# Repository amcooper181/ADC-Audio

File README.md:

# ESP32 Analog to Digital Streamer

## Overview

The **ESP32 Analog to Digital Streamer** is a project designed to capture analog audio signals and stream them using the ESP32 microcontroller. The PCM1862 ADC this project is based on is feature-rich, highly customizable, and offers a 100dB+ signal to noise ratio.

## Features

- **High-Quality Audio Capture:** Utilizes the PCM1862 ADC for precise analog-to-digital conversion.
- **Real-Time Streaming:** Stream audio data over Wi-Fi using the ESP32's built-in capabilities.
- **High Sample Rate:** 96 kHz at 24 bits
- **Low Latency:** Optimized for low-latency streaming to ensure real-time audio processing.
- **Input Options:** This device allows for inputs via a 3.5mm TRRS connector or RCA cables
- **Input Levels:** Supports line-level inputs. The PCM1862 has a configurable, 2 level gain amplifier that can be used for phono inputs, but for the best quality a dedicated, external amplifier is recommended.

## Getting Started

### Hardware

- **Prototype Stage** The KiCad files are available for the first prototype, located in [adcesp32_kicad/](./adcesp32_kicad//)
- **Power Supply** The device requires a USB-C power supply.

### Software

- **Building the Project** All files needed to build the project in PlatformIO are included in this repo
- **Basic Functionality** As of now, the software included in this repo will allow the user to convert an analog input to digital output. An I2S amplifier can be can be connected to listen to playback.
- **Buffered Data** The data is buffered before being sent to the DOUT pin on the PCM1862. This was done to prototype data processing speed.
- **Work In Progress** The software will be updated, improved, and finalized upon finalization of the hardware. The hardware is currently on order, and 5 demo boards should arrive by 9/1/2024

### License
This project is licensed under the GPL V3 License. See the [LICENSE](./LICENSE) file for details.

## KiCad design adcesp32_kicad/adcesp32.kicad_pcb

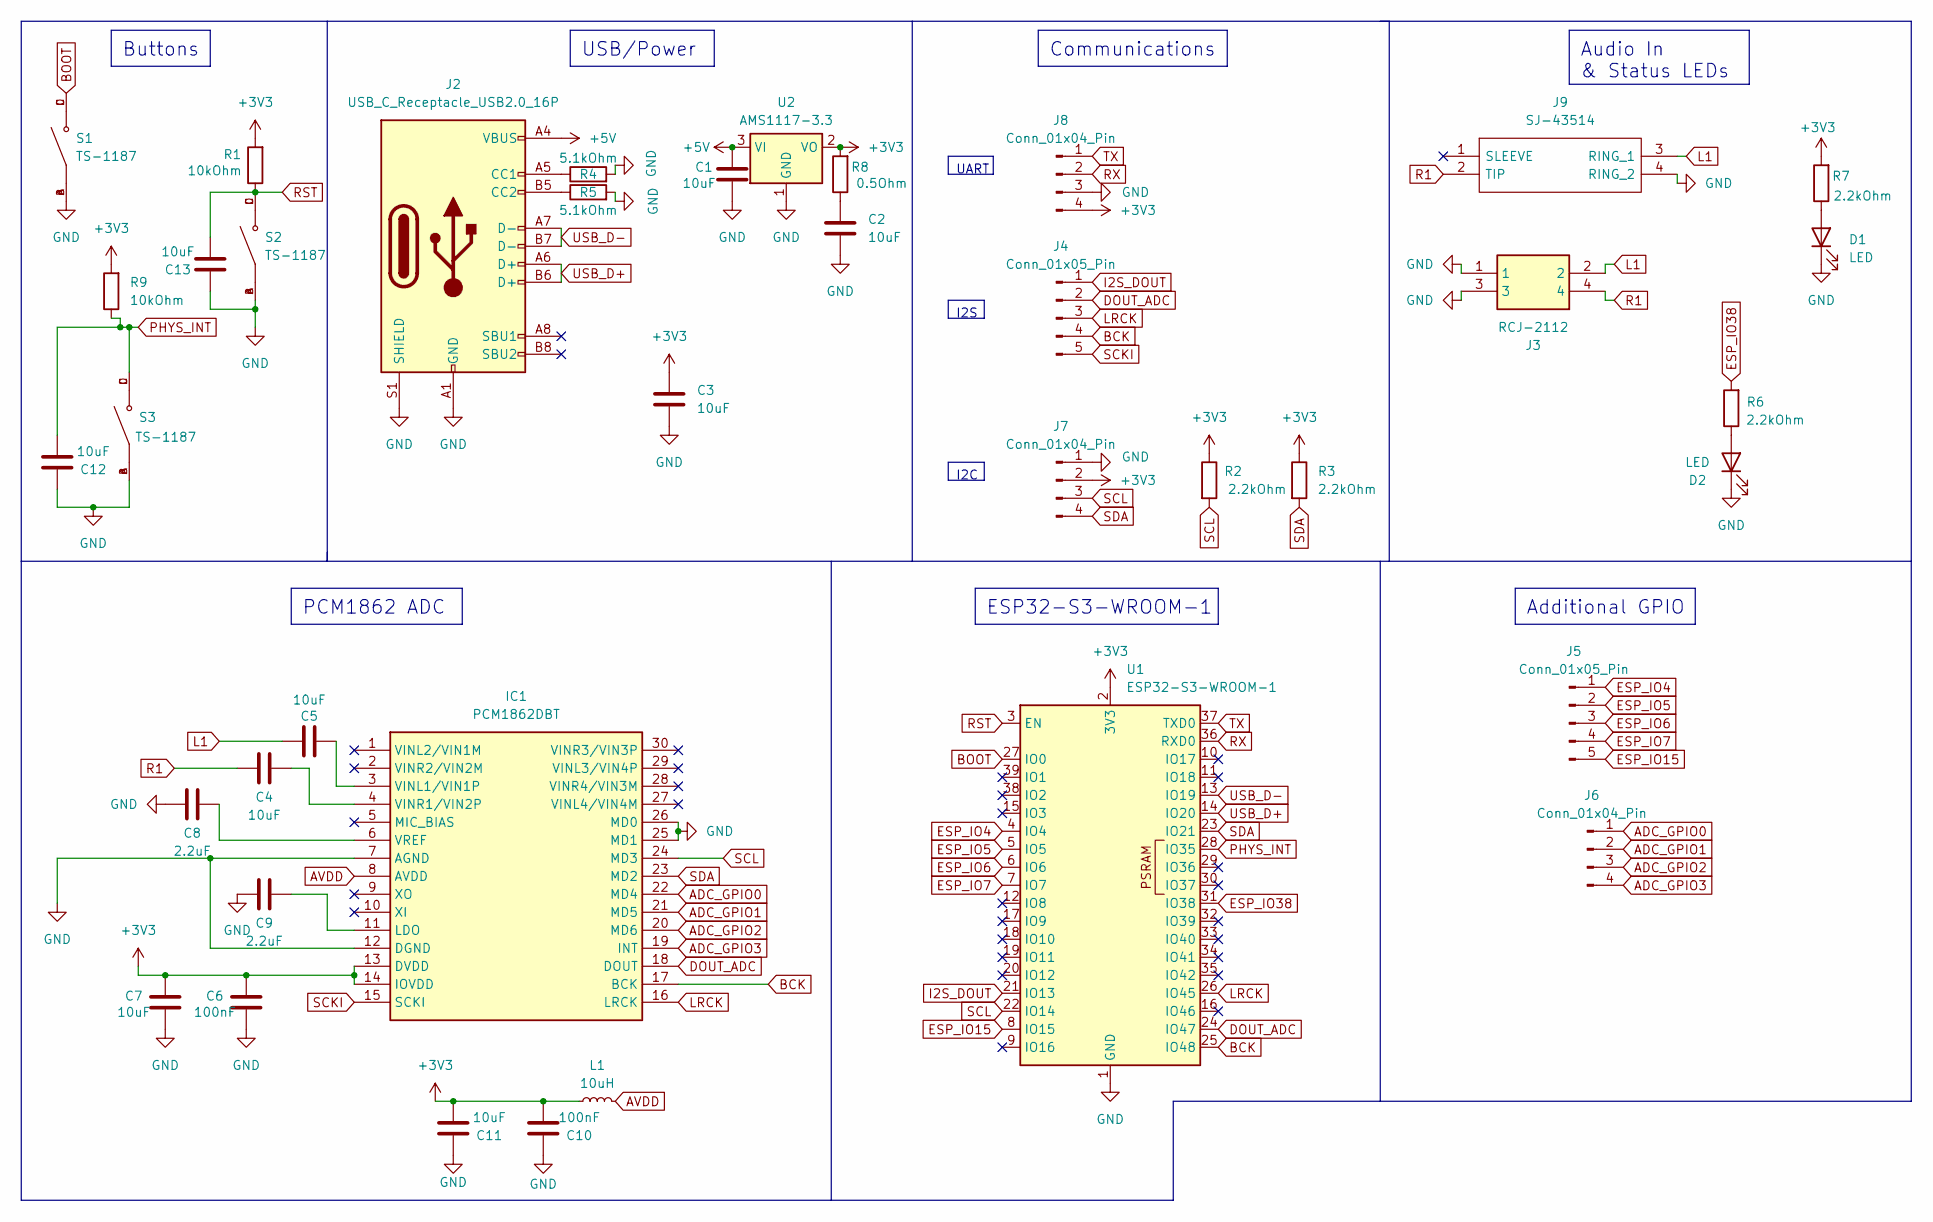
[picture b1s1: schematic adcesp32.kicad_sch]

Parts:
C1, C2, C3, C4, C5, C7, C11, C12, C13: 10uF; C_0402_1005Metric
C6, C10: 100nF; C_0402_1005Metric
C8, C9: 2.2uF; C_0402_1005Metric
D1, D2: LED; R_0805_2012Metric
IC1: PCM1862DBT; SOP50P640X120-30N; Mouser Part Number 595-PCM1862DBT
J2: USB_C_Receptacle_USB2.0_16P; USB_C_Receptacle_HRO_TYPE-C-31-M-12
J3: RCJ-2112; RCJ2112; Mouser Part Number 490-RCJ-2112
J4, J5: Conn_01x05_Pin; PinHeader_1x05_P2.54mm_Vertical
J6, J7, J8: Conn_01x04_Pin; PinHeader_1x04_P2.54mm_Vertical
J9: SJ-43514; SJ43514; Mouser Part Number 490-SJ-43514
L1: 10uH; L_0805_2012Metric
R1, R9: 10kOhm; R_0402_1005Metric
R2, R3, R6, R7: 2.2kOhm; R_0603_1608Metric
R4, R5: 5.1kOhm; R_0402_1005Metric
R8: 0.5Ohm; R_0603_1608Metric
S1, S2, S3: TS-1187; SW_TS-1187A-B-A-B; PARTREV A0
U1: ESP32-S3-WROOM-1
U2: AMS1117-3.3; SOT-223-3_TabPin2

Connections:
+3V3: C3.1, C6.2, C7.2, C10.2, C11.2, IC1.13 (DVDD), IC1.14 (IOVDD), J7.2, J8.4, L1.1, R1.2, R2.1, R3.1, R7.2, R8.2, R9.2, U1.2 (3V3), U2.2 (VO)
+5V: C1.1, J2.A4 (VBUS), J2.A9 (VBUS), J2.B4 (VBUS), J2.B9 (VBUS), U2.3 (VI)
ADC_GPIO0: IC1.22 (MD4), J6.1
ADC_GPIO1: IC1.21 (MD5), J6.2
ADC_GPIO2: IC1.20 (MD6), J6.3
ADC_GPIO3: IC1.19 (INT), J6.4
AVDD: IC1.8 (AVDD), L1.2
BCK: IC1.17 (BCK), J4.4, U1.25 (IO48)
BOOT: S1.C, S1.D, U1.27 (IO0)
DOUT_ADC: IC1.18 (DOUT), J4.2, U1.24 (IO47)
ESP_IO4: J5.1, U1.4 (IO4)
ESP_IO5: J5.2, U1.5 (IO5)
ESP_IO6: J5.3, U1.6 (IO6)
ESP_IO7: J5.4, U1.7 (IO7)
ESP_IO15: J5.5, U1.8 (IO15)
ESP_IO38: R6.2, U1.31 (IO38)
GND: C1.2, C2.2, C3.2, C6.1, C7.1, C8.1, C9.1, C10.1, C11.1, C12.1, C13.1, D1.1 (K), D2.1 (K), IC1.7 (AGND), IC1.12 (DGND), IC1.25 (MD1), IC1.26 (MD0), J2.A1 (GND), J2.A12 (GND), J2.B1 (GND), J2.B12 (GND), J2.S1 (SHIELD), J3.1, J3.3, J7.1, J8.3, J9.4 (RING_2), R4.2, R5.2, S1.A, S1.B, S2.A, S2.B, S3.A, S3.B, U1.1 (GND), U1.40 (GND), U1.41 (GND), U2.1 (GND)
I2S_DOUT: J4.1, U1.21 (IO13)
L1: C5.1, J3.2, J9.3 (RING_1)
LRCK: IC1.16 (LRCK), J4.3, U1.26 (IO45)
unnamed: C2.1, R8.1
unnamed: D1.2 (A), R7.1
unnamed: D2.2 (A), R6.1
unnamed: C9.2, IC1.11 (LDO)
unnamed: C5.2, IC1.3 (VINL1/VIN1P)
unnamed: C4.2, IC1.4 (VINR1/VIN2P)
unnamed: C8.2, IC1.6 (VREF)
unnamed: J2.A5 (CC1), R4.1
unnamed: J2.B5 (CC2), R5.1
PHYS_INT: C12.2, R9.1, S3.C, S3.D, U1.28 (IO35)
R1: C4.1, J3.4, J9.2 (TIP)
RST: C13.2, R1.1, S2.C, S2.D, U1.3 (EN)
RX: J8.2, U1.36 (RXD0)
SCKI: IC1.15 (SCKI), J4.5
SCL: IC1.24 (MD3), J7.3, R2.2, U1.22 (IO14)
SDA: IC1.23 (MD2), J7.4, R3.2, U1.23 (IO21)
TX: J8.1, U1.37 (TXD0)
USB_D+: J2.A6 (D+), J2.B6 (D+), U1.14 (IO20)
USB_D-: J2.A7 (D-), J2.B7 (D-), U1.13 (IO19)

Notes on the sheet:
Buttons
UART
Additional GPIO
I2C
I2S
PCM1862 ADC
Communications
Audio In & Status LEDs
ESP32-S3-WROOM-1
USB/Power

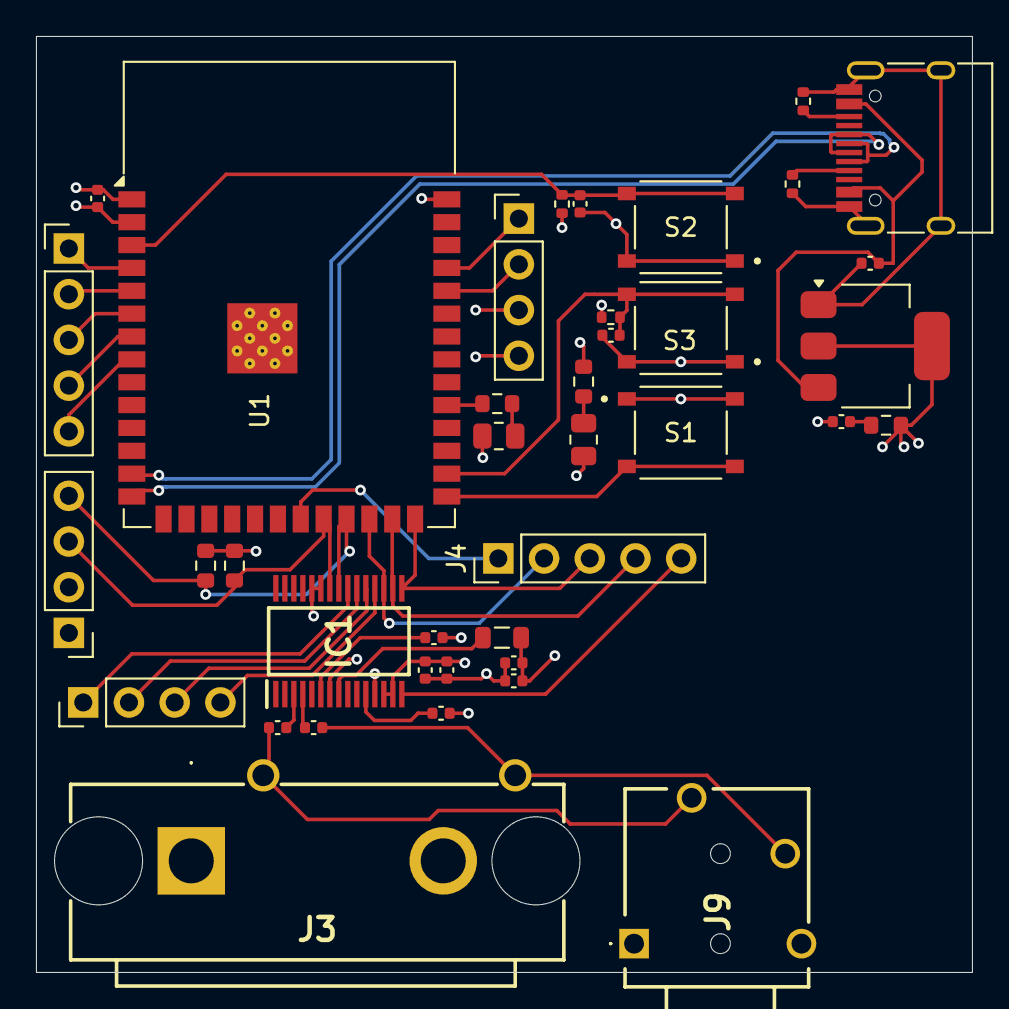
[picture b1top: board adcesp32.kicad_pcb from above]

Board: 4 copper layers, 52.0 x 52.0 mm, 39 parts (0 on the bottom side), 39 nets.

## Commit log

2024-07-12 Added writeRegister method.
2024-07-31 basic i2s is operational
2024-07-31 fixed 96khz sampling
2024-07-31 updated .gitignore
2024-07-31 added kicad files
2024-08-01 updated schematic
2024-08-01 added cap values
2024-08-02 completed pcb design
2024-08-10 completed 52x52 pcb design
2024-08-10 removed grbr/drl
2024-08-10 added license and readme
